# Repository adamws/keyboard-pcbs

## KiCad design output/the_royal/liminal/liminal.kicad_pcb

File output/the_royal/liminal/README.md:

## the_royal/liminal

[layout](liminal-kle.json) - [PCB](liminal.kicad_pcb)

{:loading="lazy"}

[Open in keyboard-layout-editor](http://www.keyboard-layout-editor.com/##@@_x:2.5&c=#777777;&=0,0&_c=#aaaaaa&w:1.5;&=0,1&_c=#cccccc;&=0,2&=0,3&=0,4&=0,5&=0,6&=0,7&=0,8&=0,9&=0,10&=0,11&=0,12&_c=#aaaaaa&w:1.5;&=0,13%0A%0A%0A0,0;&@_x:2.5;&=1,0&_w:1.75;&=1,1&_c=#cccccc;&=1,2&=1,3&=1,4&=1,5&=1,6&=1,7&=1,8&=1,9&=1,10&=1,11&_c=#777777&w:2.25;&=1,13%0A%0A%0A0,0;&@_x:2.5&c=#aaaaaa;&=2,0&_w:2.25;&=2,1%0A%0A%0A1,0&_c=#cccccc;&=2,3&=2,4&=2,5&=2,6&=2,7&=2,8&=2,9&=2,10&=2,11&=2,12&_c=#aaaaaa&w:1.75;&=2,13;&@_x:2.5;&=3,0%0A%0A%0A2,0&_w:1.25;&=3,1%0A%0A%0A2,0&=3,2%0A%0A%0A2,0&_w:1.25;&=3,3%0A%0A%0A2,0&_c=#cccccc&w:7;&=3,7%0A%0A%0A2,0&_c=#aaaaaa&w:1.25;&=3,10%0A%0A%0A2,0&=3,12%0A%0A%0A2,0&_w:1.25;&=3,13%0A%0A%0A2,0;&@_x:18.75&y:-4&c=#777777&w:1.25&h:2&w2:1.5&h2:1&x2:-0.25;&=0,13%0A%0A%0A0,1&_x:1.0&c=#aaaaaa&w:1.5;&=0,13%0A%0A%0A0,2;&@_x:17.75&c=#cccccc;&=1,12%0A%0A%0A0,1&_x:1.5;&=1,12%0A%0A%0A0,2&_c=#777777&w:1.25;&=1,13%0A%0A%0A0,2;&@_c=#aaaaaa&w:1.25;&=2,1%0A%0A%0A1,1&_c=#cccccc;&=2,2%0A%0A%0A1,1;&@_x:2.5&y:1.5&c=#aaaaaa;&=3,0%0A%0A%0A2,1&_w:1.5;&=3,1%0A%0A%0A2,1&_w:1.25;&=3,2%0A%0A%0A2,1&_w:1.5;&=3,3%0A%0A%0A2,1&_c=#cccccc&w:2;&=3,5%0A%0A%0A2,1&_w:2.25;&=3,7%0A%0A%0A2,1&_c=#aaaaaa&w:1.5;&=3,9%0A%0A%0A2,1&_w:1.25;&=3,10%0A%0A%0A2,1&_w:1.25;&=3,12%0A%0A%0A2,1&_w:1.5;&=3,13%0A%0A%0A2,1)

{:loading="lazy"}

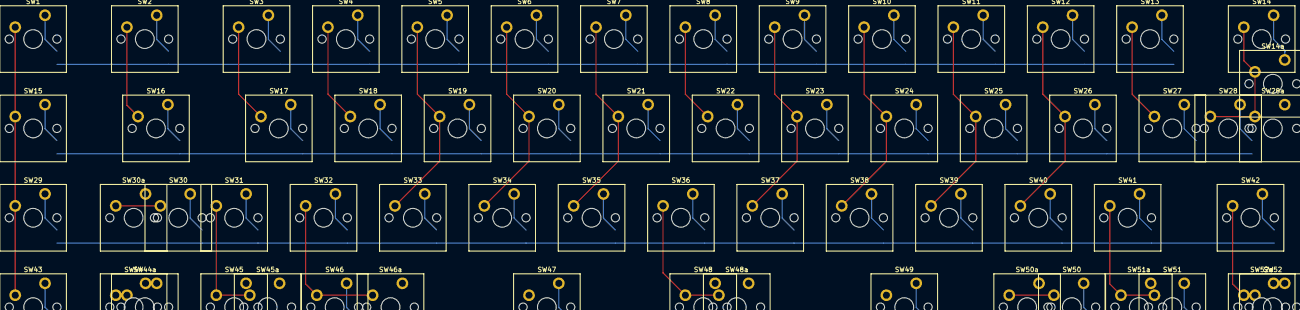
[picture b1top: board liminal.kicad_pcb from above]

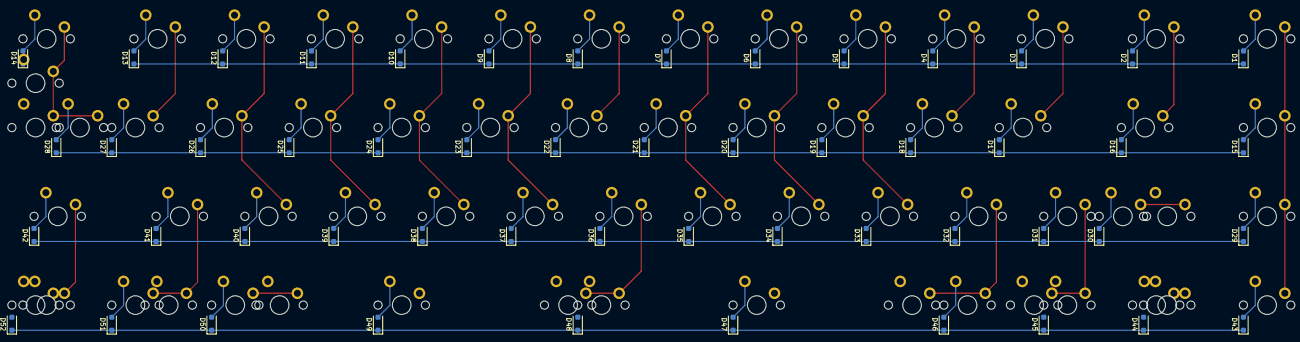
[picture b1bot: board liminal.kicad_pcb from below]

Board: 2 copper layers, 114 parts (52 on the bottom side), 70 nets.

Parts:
D1, D2, D3, D4, D5, D6, D7, D8, D9, D10, D11, D12, D13, D14, D15, D16, D17, D18, D19, D20, D21, D22, D23, D24, D25, D26, D27, D28, D29, D30, D31, D32, D33, D34, D35, D36, D37, D38, D39, D40, D41, D42, D43, D44, D45, D46, D47, D48, D49, D50, D51, D52: D_SOD-123F
SW1, SW2, SW3, SW4, SW5, SW6, SW7, SW8, SW9, SW10, SW11, SW12, SW13, SW14, SW14a, SW15, SW16, SW17, SW18, SW19, SW20, SW21, SW22, SW23, SW24, SW25, SW26, SW27, SW28, SW28a, SW29, SW30, SW30a, SW31, SW32, SW33, SW34, SW35, SW36, SW37, SW38, SW39, SW40, SW41, SW42, SW43, SW44, SW44a, SW45, SW45a, SW46, SW46a, SW47, SW48, SW48a, SW49, SW50, SW50a, SW51, SW51a, SW52, SW52a: SW_Cherry_MX_PCB_1.00u

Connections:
COL0: SW1.1, SW15.1, SW29.1, SW43.1
COL1: SW2.1, SW16.1, SW30.1, SW30a.1, SW44.1, SW44a.1
COL2: SW3.1, SW17.1, SW31.1, SW45.1, SW45a.1
COL3: SW4.1, SW18.1, SW32.1, SW46.1, SW46a.1
COL4: SW5.1, SW19.1, SW33.1
COL5: SW6.1, SW20.1, SW34.1, SW47.1
COL6: SW7.1, SW21.1, SW35.1
COL7: SW8.1, SW22.1, SW36.1, SW48.1, SW48a.1
COL8: SW9.1, SW23.1, SW37.1
COL9: SW10.1, SW24.1, SW38.1, SW49.1
COL10: SW11.1, SW25.1, SW39.1, SW50.1, SW50a.1
COL11: SW12.1, SW26.1, SW40.1
COL12: SW13.1, SW27.1, SW41.1, SW51.1, SW51a.1
COL13: SW14.1, SW14a.1, SW28.1, SW28a.1, SW42.1, SW52.1, SW52a.1
unnamed: D1.2, SW1.2
unnamed: D2.2, SW2.2
unnamed: D3.2, SW3.2
unnamed: D4.2, SW4.2
unnamed: D5.2, SW5.2
unnamed: D6.2, SW6.2
unnamed: D7.2, SW7.2
unnamed: D8.2, SW8.2
unnamed: D9.2, SW9.2
unnamed: D10.2, SW10.2
unnamed: D11.2, SW11.2
unnamed: D12.2, SW12.2
unnamed: D13.2, SW13.2
unnamed: D14.2, SW14.2, SW14a.2
unnamed: D15.2, SW15.2
unnamed: D16.2, SW16.2
unnamed: D17.2, SW17.2
unnamed: D18.2, SW18.2
unnamed: D19.2, SW19.2
unnamed: D20.2, SW20.2
unnamed: D21.2, SW21.2
unnamed: D22.2, SW22.2
unnamed: D23.2, SW23.2
unnamed: D24.2, SW24.2
unnamed: D25.2, SW25.2
unnamed: D26.2, SW26.2
unnamed: D27.2, SW27.2
unnamed: D28.2, SW28.2, SW28a.2
unnamed: D29.2, SW29.2
unnamed: D30.2, SW30.2, SW30a.2
unnamed: D31.2, SW31.2
unnamed: D32.2, SW32.2
unnamed: D33.2, SW33.2
unnamed: D34.2, SW34.2
unnamed: D35.2, SW35.2
unnamed: D36.2, SW36.2
unnamed: D37.2, SW37.2
unnamed: D38.2, SW38.2
unnamed: D39.2, SW39.2
unnamed: D40.2, SW40.2
unnamed: D41.2, SW41.2
unnamed: D42.2, SW42.2
unnamed: D43.2, SW43.2
unnamed: D44.2, SW44.2, SW44a.2
unnamed: D45.2, SW45.2, SW45a.2
unnamed: D46.2, SW46.2, SW46a.2
unnamed: D47.2, SW47.2
unnamed: D48.2, SW48.2, SW48a.2
unnamed: D49.2, SW49.2
unnamed: D50.2, SW50.2, SW50a.2
unnamed: D51.2, SW51.2, SW51a.2
unnamed: D52.2, SW52.2, SW52a.2
ROW0: D1.1, D2.1, D3.1, D4.1, D5.1, D6.1, D7.1, D8.1, D9.1, D10.1, D11.1, D12.1, D13.1, D14.1
ROW1: D15.1, D16.1, D17.1, D18.1, D19.1, D20.1, D21.1, D22.1, D23.1, D24.1, D25.1, D26.1, D27.1, D28.1
ROW2: D29.1, D30.1, D31.1, D32.1, D33.1, D34.1, D35.1, D36.1, D37.1, D38.1, D39.1, D40.1, D41.1, D42.1
ROW3: D43.1, D44.1, D45.1, D46.1, D47.1, D48.1, D49.1, D50.1, D51.1, D52.1
